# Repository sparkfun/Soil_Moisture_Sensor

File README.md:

SparkFun Soil Moisture Sensor 
=============================

<table class="table table-hover table-striped table-bordered">
  <tr align="center">
   <td></td>
   <td></td>
  </tr>
  <tr align="center">
   <td><i>SparkFun Soil Moisture Sensor [<a href="https://www.sparkfun.com/products/13322">SEN-13322</a>]</i></td>
   <td><i>SparkFun Soil Moisture Sensor (with Screw Terminals) [<a href="https://www.sparkfun.com/products/SEN-13637">SEN-13637</a>]</i></td>
  </tr>
</table>

A simple breakout to aid in the measuring of moisture in soil and similar materials. 

Repository Contents
-------------------

* **/Hardware** - Eagle design files (.brd, .sch)
* **/Production** - Production panel files (.brd)

Documentation
--------------

* **[Hookup Guide](https://learn.sparkfun.com/tutorials/soil-moisture-sensor-hookup-guide)** - Basic hookup guide for the Soil Moisture Sensor.
* **[SparkFun Fritzing repo](https://github.com/sparkfun/Fritzing_Parts/blob/main/products/13322_sfe_soil_moisture_sensor.fzpz) (without Screw Terminals)** - Fritzing diagrams for SparkFun products.
* **[SparkFun 3D Model repo](https://github.com/sparkfun/3D_Models)** - 3D models of SparkFun products. 

Product Versions
----------------

* [SEN-13637](https://www.sparkfun.com/products/13637) - v1.0, with screw terminals
* [SEN-13322](https://www.sparkfun.com/products/13322) - Initial Release, v1.0

License Information
-------------------

This product is _**open source**_! 

Please review the LICENSE.md file for license information. 

If you have any questions or concerns on licensing, please contact techsupport@sparkfun.com.

Distributed as-is; no warranty is given.

- Your friends at SparkFun.

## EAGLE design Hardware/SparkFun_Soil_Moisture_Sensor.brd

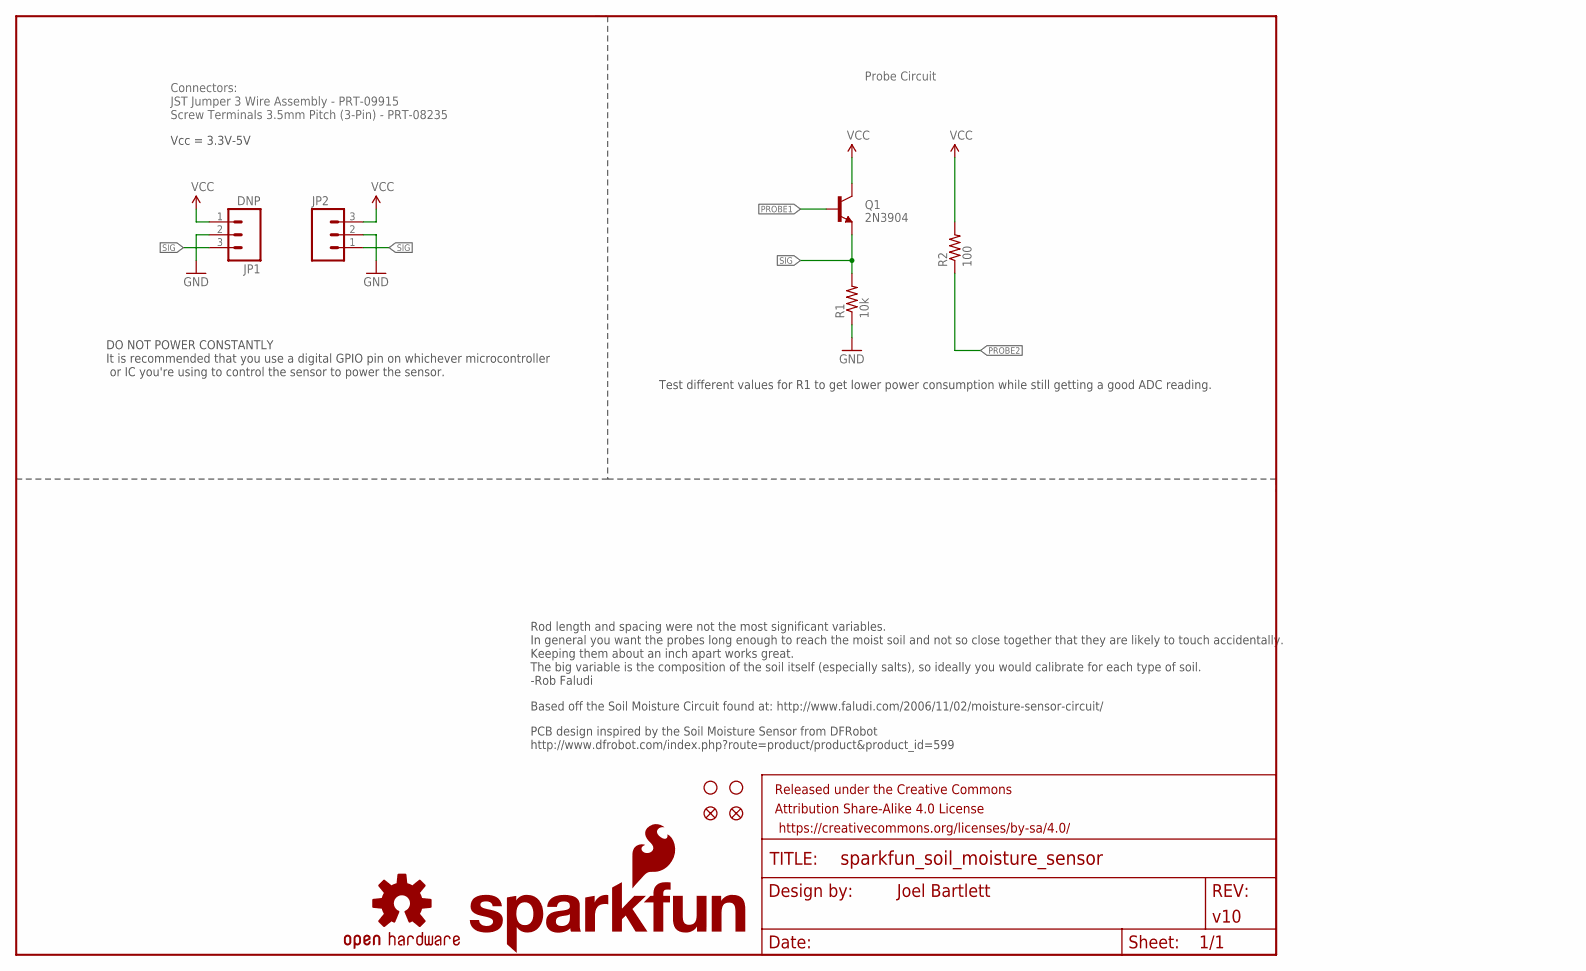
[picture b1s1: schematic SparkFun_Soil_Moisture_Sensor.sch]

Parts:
FID1, FID2: FIDUCIAL1X2; FIDUCIAL-1X2
FRAME1: FRAME-LETTER; CREATIVE_COMMONS
JP1: DNP; MOLEX-1X3
JP2: M03SCREW_LOCK; SCREWTERMINAL-3.5MM-3_LOCK.007S
LOGO1: SFE_LOGO_NAME_FLAME.1_INCH; SFE_LOGO_NAME_FLAME_.1
LOGO2: OSHW-LOGOS; OSHW-LOGO-S
Q1: 2N3904; SOT23-3
R1: 10k; 0603-RES
R2: 100; 0603-RES
STANDOFF1, STANDOFF2: STAND-OFF

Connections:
GND: JP1.2, JP2.2, R1.1
PROBE1: Q1.1 (B)
PROBE2: R2.1
SIG: JP1.3, JP2.1, Q1.2 (E), R1.2
VCC: JP1.1, JP2.3, Q1.3 (C), R2.2

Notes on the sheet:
Test different values for R1 to get lower power consumption while still getting a good ADC reading.
Based off the Soil Moisture Circuit found at: http://www.faludi.com/2006/11/02/moisture-sensor-circuit/
Rod length and spacing were not the most significant variables. In general you want the probes long enough to reach the moist soil and not so close together that they are likely to touch accidentally. Keeping them about an inch apart works great. The big variable is the composition of the soil itse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
Connectors: JST Jumper 3 Wire Assembly - PRT-09915 Screw Terminals 3.5mm Pitch (3-Pin) - PRT-08235
Probe Circuit
Vcc = 3.3V-5V
DO NOT POWER CONSTANTLY It is recommended that you use a digital GPIO pin on whichever microcontroller or IC you're using to control the sensor to power the sensor.
PCB design inspired by the Soil Moisture Sensor from DFRobot http://www.dfrobot.com/index.php?route=product/product&product_id=599

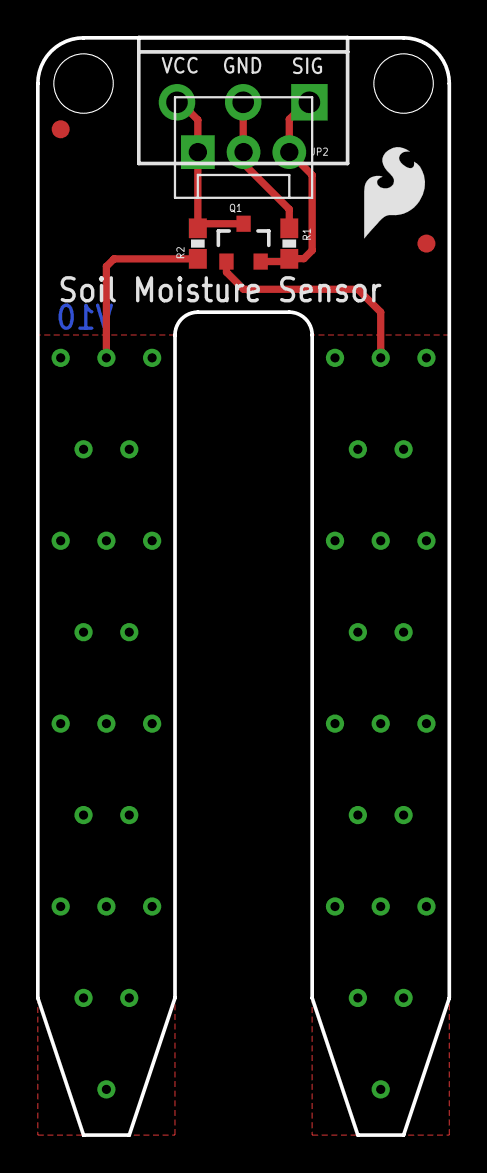
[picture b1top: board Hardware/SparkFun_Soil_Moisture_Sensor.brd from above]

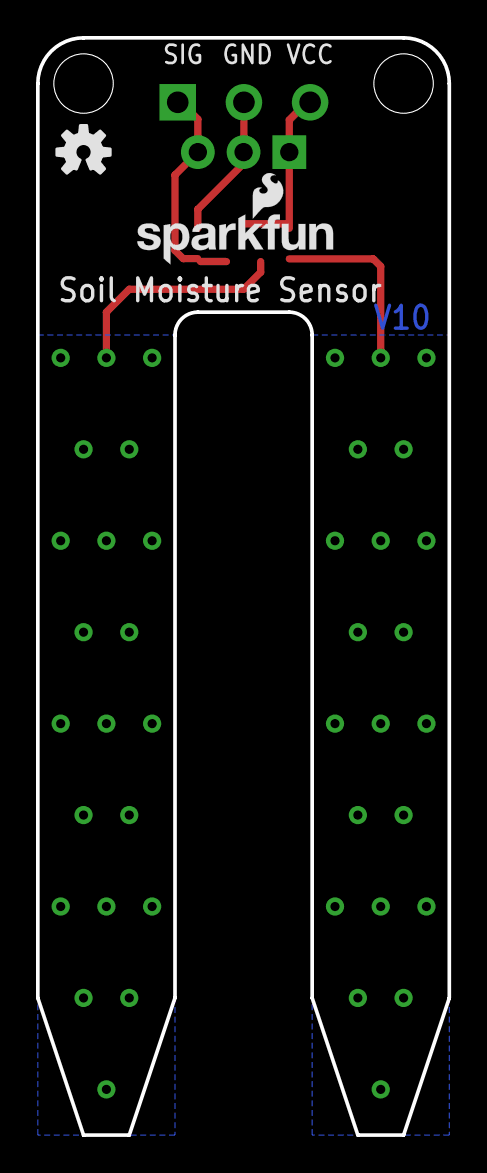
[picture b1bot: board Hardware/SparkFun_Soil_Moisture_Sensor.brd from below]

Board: 2 copper layers, 22.9 x 61.0 mm, 13 parts (2 on the bottom side), 3 nets.

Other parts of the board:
U$4: SFE_LOGO_FLAME_.2

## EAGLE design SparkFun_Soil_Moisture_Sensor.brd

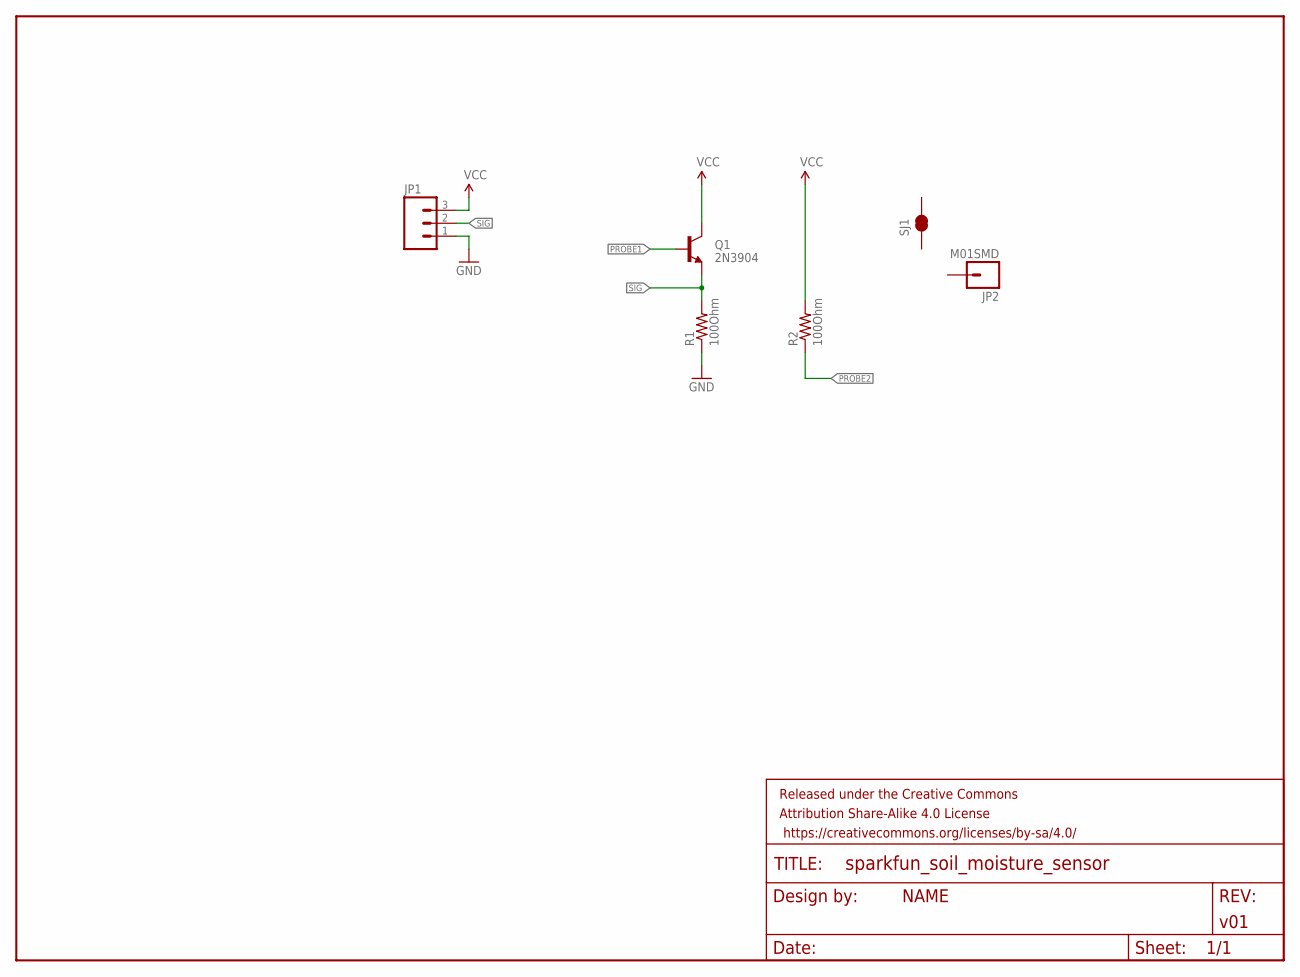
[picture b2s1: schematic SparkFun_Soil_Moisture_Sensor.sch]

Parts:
FRAME1: FRAME-LETTER; CREATIVE_COMMONS
JP1: M03PTH; 1X03
JP2: M01SMD; LUXEON-PAD
Q1: 2N3904; SOT23-3
R1, R2: 100Ohm; 0603-RES
SJ1: JUMPER-PAD-2-NC_BY_TRACE; PAD-JUMPER-2-NC_BY_TRACE_YES_SILK

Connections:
GND: JP1.1, R1.1
PROBE1: Q1.1 (B)
PROBE2: R2.1
SIG: JP1.2, Q1.2 (E), R1.2
VCC: JP1.3, Q1.3 (C), R2.2

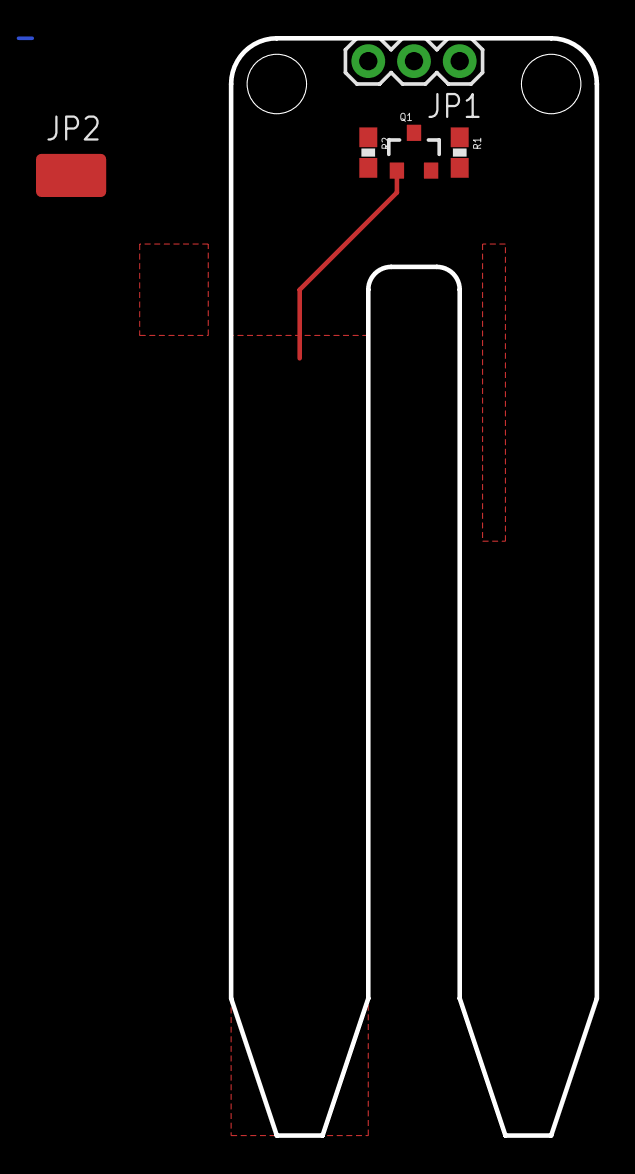
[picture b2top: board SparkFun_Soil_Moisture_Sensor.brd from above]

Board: 2 copper layers, 20.3 x 61.0 mm, 9 parts (1 on the bottom side), 3 nets.

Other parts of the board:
U$1, U$2: STAND-OFF

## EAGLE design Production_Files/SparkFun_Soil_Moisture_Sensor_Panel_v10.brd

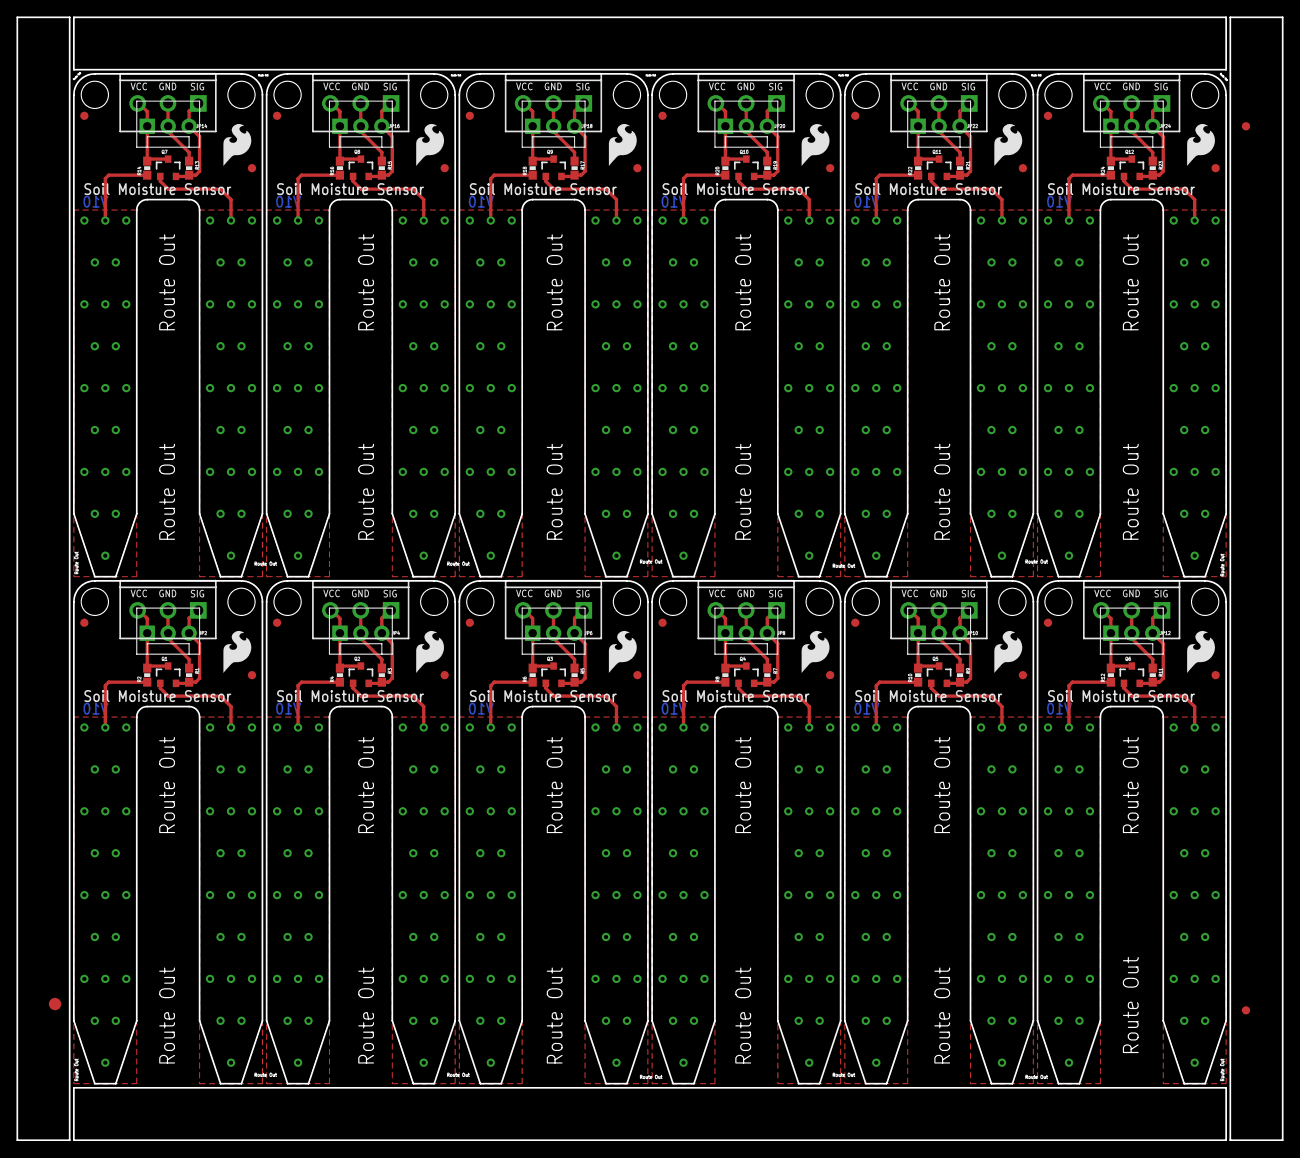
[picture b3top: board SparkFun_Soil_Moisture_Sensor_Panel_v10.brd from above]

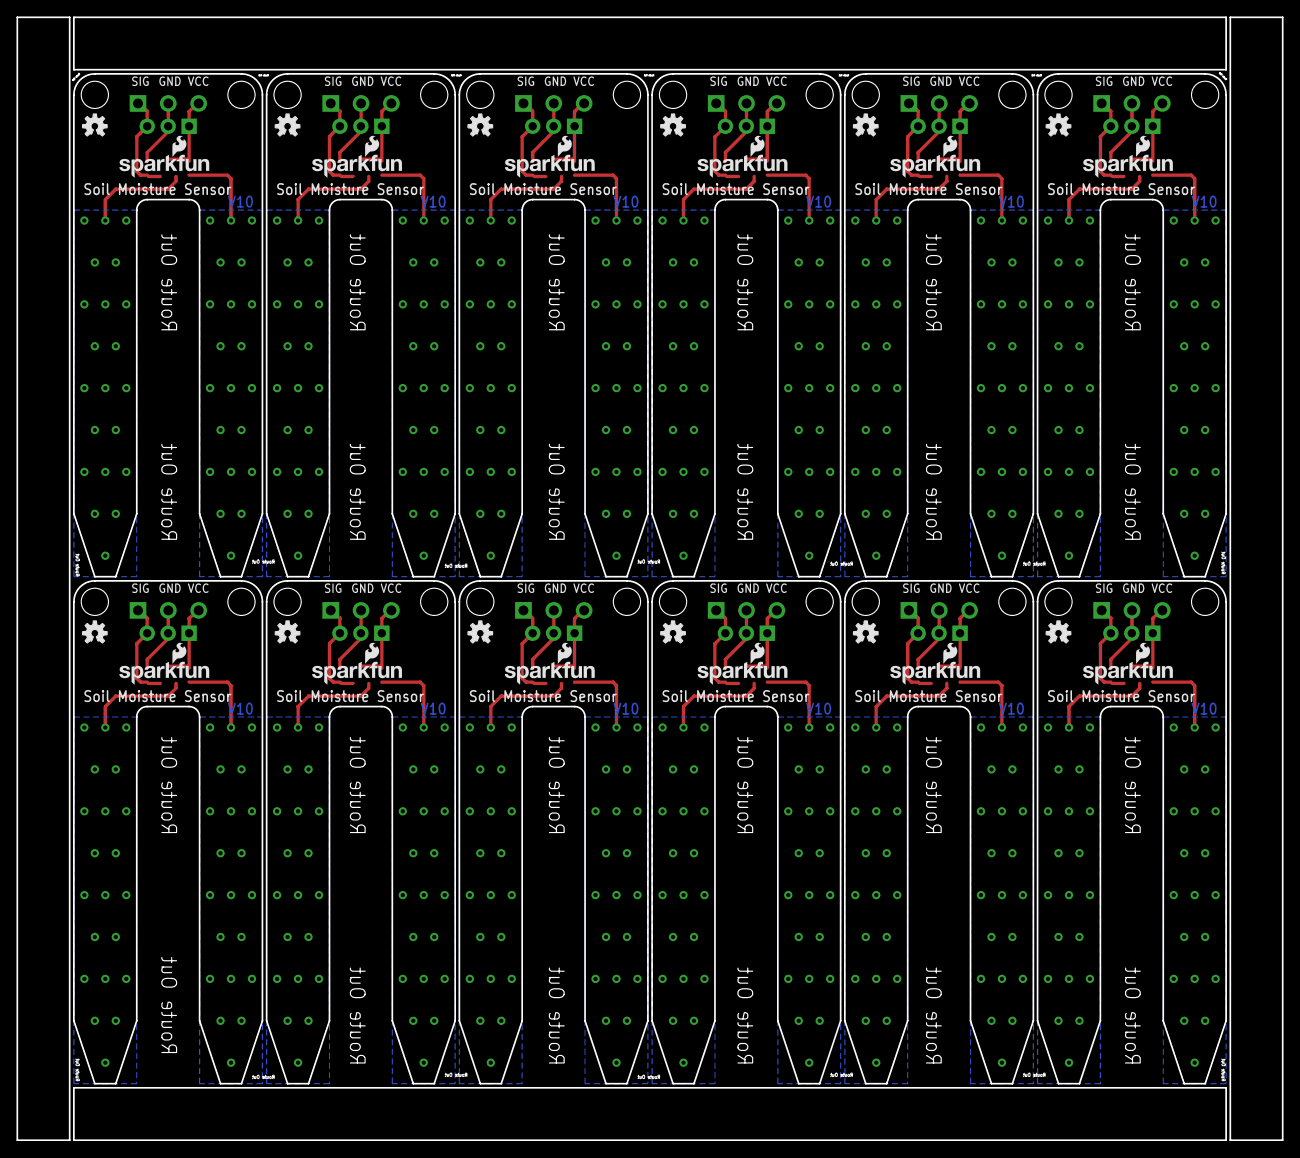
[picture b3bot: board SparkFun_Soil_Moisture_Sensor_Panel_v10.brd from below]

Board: 2 copper layers, 153.4 x 136.1 mm, 147 parts (24 on the bottom side), 36 nets.

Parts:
E$1: FIDUCIAL-1.5X3
E$4, E$5: FIDUCIAL-1X2
FID1, FID2, FID3, FID4, FID5, FID6, FID7, FID8, FID9, FID10, FID11, FID12, FID13, FID14, FID15, FID16, FID17, FID18, FID19, FID20, FID21, FID22, FID23, FID24: FIDUCIAL1X2; FIDUCIAL-1X2
JP1, JP3, JP5, JP7, JP9, JP11, JP13, JP15, JP17, JP19, JP21, JP23: DNP; MOLEX-1X3
JP2, JP4, JP6, JP8, JP10, JP12, JP14, JP16, JP18, JP20, JP22, JP24: SCREWTERMINAL-3.5MM-3_LOCK.007S
LOGO1, LOGO3, LOGO5, LOGO7, LOGO9, LOGO11, LOGO13, LOGO15, LOGO17, LOGO19, LOGO21, LOGO23: SFE_LOGO_NAME_FLAME.1_INCH; SFE_LOGO_NAME_FLAME_.1
LOGO2, LOGO4, LOGO6, LOGO8, LOGO10, LOGO12, LOGO14, LOGO16, LOGO18, LOGO20, LOGO22, LOGO24: OSHW-LOGOS; OSHW-LOGO-S
Q1, Q2, Q3, Q4, Q5, Q6, Q7, Q8, Q9, Q10, Q11, Q12: 2N3904; SOT23-3
R1, R3, R5, R7, R9, R11, R13, R15, R17, R19, R21, R23: 10k; 0603-RES
R2, R4, R6, R8, R10, R12, R14, R16, R18, R20, R22, R24: 100; 0603-RES
STANDOFF1, STANDOFF2, STANDOFF3, STANDOFF4, STANDOFF5, STANDOFF6, STANDOFF7, STANDOFF8, STANDOFF9, STANDOFF10, STANDOFF11, STANDOFF12, STANDOFF13, STANDOFF14, STANDOFF15, STANDOFF16, STANDOFF17, STANDOFF18, STANDOFF19, STANDOFF20, STANDOFF21, STANDOFF22, STANDOFF23, STANDOFF24: STAND-OFF
U$1, U$2, U$3, U$4, U$5, U$6, U$7, U$8, U$9, U$10, U$11, U$12: SFE_LOGO_FLAME_.2

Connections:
GND: JP1.2, JP2.2, R1.1
GND1: JP3.2, JP4.2, R3.1
GND2: JP5.2, JP6.2, R5.1
GND3: JP7.2, JP8.2, R7.1
GND4: JP9.2, JP10.2, R9.1
GND5: JP11.2, JP12.2, R11.1
GND6: JP13.2, JP14.2, R13.1
GND7: JP15.2, JP16.2, R15.1
GND8: JP17.2, JP18.2, R17.1
GND9: JP19.2, JP20.2, R19.1
GND10: JP21.2, JP22.2, R21.1
GND11: JP23.2, JP24.2, R23.1
SIG: JP1.3, JP2.1, Q1.2, R1.2
SIG1: JP3.3, JP4.1, Q2.2, R3.2
SIG2: JP5.3, JP6.1, Q3.2, R5.2
SIG3: JP7.3, JP8.1, Q4.2, R7.2
SIG4: JP9.3, JP10.1, Q5.2, R9.2
SIG5: JP11.3, JP12.1, Q6.2, R11.2
SIG6: JP13.3, JP14.1, Q7.2, R13.2
SIG7: JP15.3, JP16.1, Q8.2, R15.2
SIG8: JP17.3, JP18.1, Q9.2, R17.2
SIG9: JP19.3, JP20.1, Q10.2, R19.2
SIG10: JP21.3, JP22.1, Q11.2, R21.2
SIG11: JP23.3, JP24.1, Q12.2, R23.2
VCC: JP1.1, JP2.3, Q1.3, R2.2
VCC1: JP3.1, JP4.3, Q2.3, R4.2
VCC2: JP5.1, JP6.3, Q3.3, R6.2
VCC3: JP7.1, JP8.3, Q4.3, R8.2
VCC4: JP9.1, JP10.3, Q5.3, R10.2
VCC5: JP11.1, JP12.3, Q6.3, R12.2
VCC6: JP13.1, JP14.3, Q7.3, R14.2
VCC7: JP15.1, JP16.3, Q8.3, R16.2
VCC8: JP17.1, JP18.3, Q9.3, R18.2
VCC9: JP19.1, JP20.3, Q10.3, R20.2
VCC10: JP21.1, JP22.3, Q11.3, R22.2
VCC11: JP23.1, JP24.3, Q12.3, R24.2

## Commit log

2015-02-17 Adding .brd and .sch files
    Adding .brd and .sch files
2015-02-23 Adding Hardware Files
    Adding Hardware Files
2015-02-26 V10
    V10 prototype
2015-03-02 Soil moisture sensor v10 prototype
    Soil moisture sensor v10 prototype
2015-03-03 adding tstop
    adding tstop
2015-03-04 Fixed QC Checklist issues
    added fiducials, changed dimension width to .008, removed Ohm from
    values, added Vcc range, changed version # to correct V01, corrected
    dashed lines
2015-05-04 Ready for QC checklist
    thickened traces, few minor aesthetic changes. Updated version #.
2015-05-05 Ready for Reds
    Passed QC check #2
    -Comments to layer 97
    -Updated Version # on SCH.
2015-05-08 Added Locking 3-pin 3.5mm footprint
    Added Locking 3-pin 3.5mm footprint for selective soldering.
2015-05-11 created panel v10
2015-09-08 Adding license file, updating README, cleaning up repo structure

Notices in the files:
parts and their libraries:
SparkFun-DiscreteSemi: Licensing: Creative Commons ShareAlike 4.0 International - https://creativecommons.org/licenses/by-sa/4.0
SparkFun-Aesthetics: Released under the Creative Commons Attribution Share-Alike 4.0 License
SparkFun-Aesthetics: https://creativecommons.org/licenses/by-sa/4.0
